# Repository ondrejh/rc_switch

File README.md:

RC signal (PWM) driven load switch
==================================

## Description

The device is using small mcu (cheapest possible MSP430FR2000) to decode RC signal and switch on the load NMOS tranzistor. Therefor its NPN switch (switching - or gnd).

PCB has no connectors. The servo (3 wires), battery (2 wires) and load (2 wires) cables are soldered directly to solder pads to save space and wheight.

The signal treshold and hysteresis is set in the code (see [main.c](/fw/main.c)). The polarity switching (high or low) can be set by soldering bridge marked "NEG".

## Hardware

### Schematic:

### Assembled printed circuit (visualisation):

## ToDo:

- describe make process and tools
- describe programming
- create GIF demo

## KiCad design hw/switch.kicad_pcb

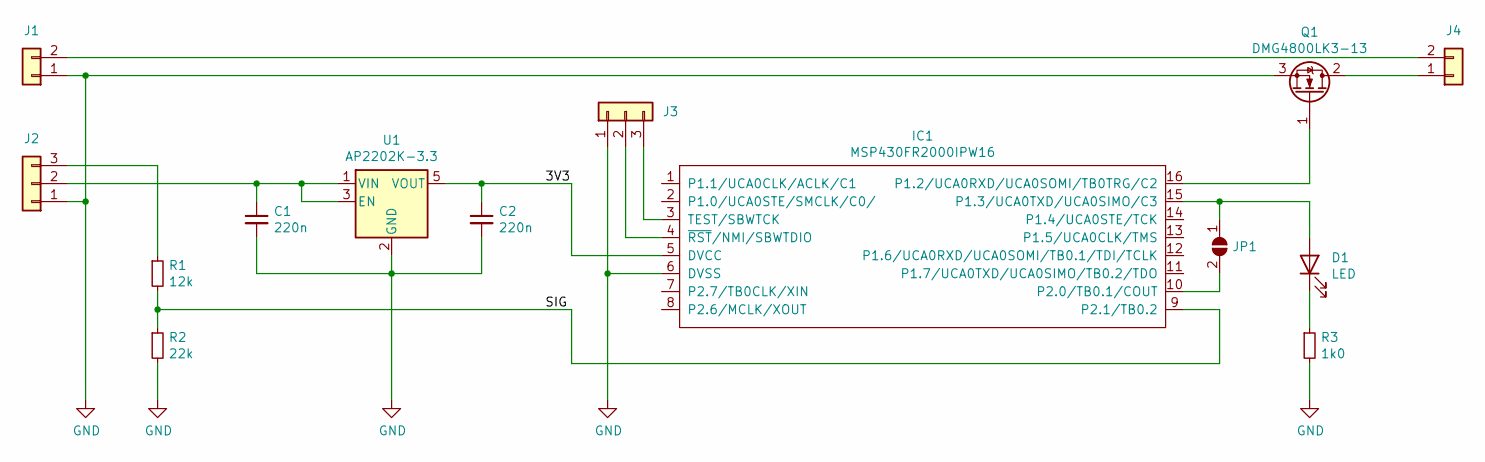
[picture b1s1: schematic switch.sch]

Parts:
C1, C2: 220n; C_0805_2012Metric
D1: LED; LED_0603_1608Metric
IC1: MSP430FR2000IPW16; TSSOP-16_4.4x5mm_P0.65mm
J1, J4: Conn_01x02; PWR_CON
J2: Conn_01x03; SERVO
J3: Conn_01x03; PROG
JP1: SolderJumper_2_Open; SolderJumper-2_P1.3mm_Open_Pad1.0x1.5mm
Q1: DMG4800LK3-13; TO-252-3_TabPin2
R1: 12k; R_0603_1608Metric
R2: 22k; R_0603_1608Metric
R3: 1k0; R_0603_1608Metric
U1: AP2202K-3.3; SOT-23-5

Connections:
/3V3: C2.1, IC1.5 (DVCC), U1.5 (VOUT)
/SIG: IC1.9 (P2.1/TB0.2), R1.2, R2.1
GND: C1.2, C2.2, IC1.6 (DVSS), J1.1, J2.1, J3.1, Q1.3 (S), R2.2, R3.2, U1.2 (GND)
unnamed: C1.1, J2.2, U1.1 (VIN), U1.3 (EN)
unnamed: D1.1 (K), R3.1
unnamed: D1.2 (A), IC1.15 (P1.3/UCA0TXD/UCA0SIMO/C3), JP1.1 (A)
unnamed: IC1.3 (TEST/SBWTCK), J3.3
unnamed: IC1.4 (~RST~/NMI/SBWTDIO), J3.2
unnamed: IC1.10 (P2.0/TB0.1/COUT), JP1.2 (B)
unnamed: IC1.16 (P1.2/UCA0RXD/UCA0SOMI/TB0TRG/C2), Q1.1 (G)
unnamed: J1.2, J4.2
unnamed: J2.3, R1.1
unnamed: J4.1, Q1.2 (D)

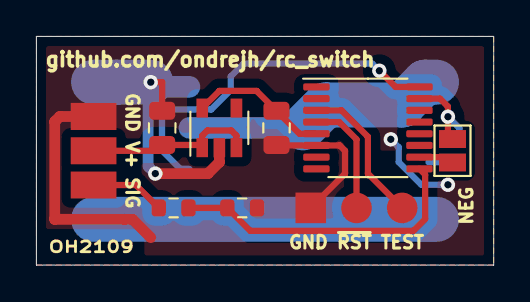
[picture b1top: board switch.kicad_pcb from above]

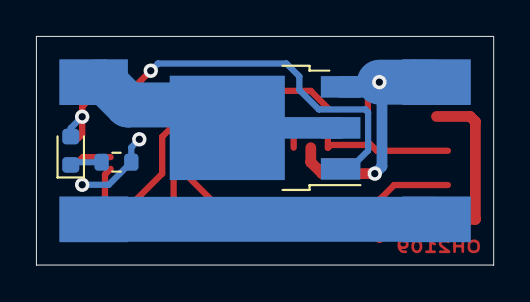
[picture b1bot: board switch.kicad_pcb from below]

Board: 2 copper layers, 25.4 x 12.7 mm, 14 parts (5 on the bottom side), 13 nets.

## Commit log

2021-09-13 repo name
2021-09-16 fw (copied from different project)
2021-09-16 gerber data
2021-10-20 bom update
2021-10-20 switch to MSP430Flasher, test programmig
2021-10-20 change target name
2021-10-20 uz to funguje
2021-11-02 2 more tranzistors - preffered YJD20N06A
2021-11-02 README
2021-11-02 improve images
2021-11-02 newlines
2021-11-02 more description
2021-11-02 todo
